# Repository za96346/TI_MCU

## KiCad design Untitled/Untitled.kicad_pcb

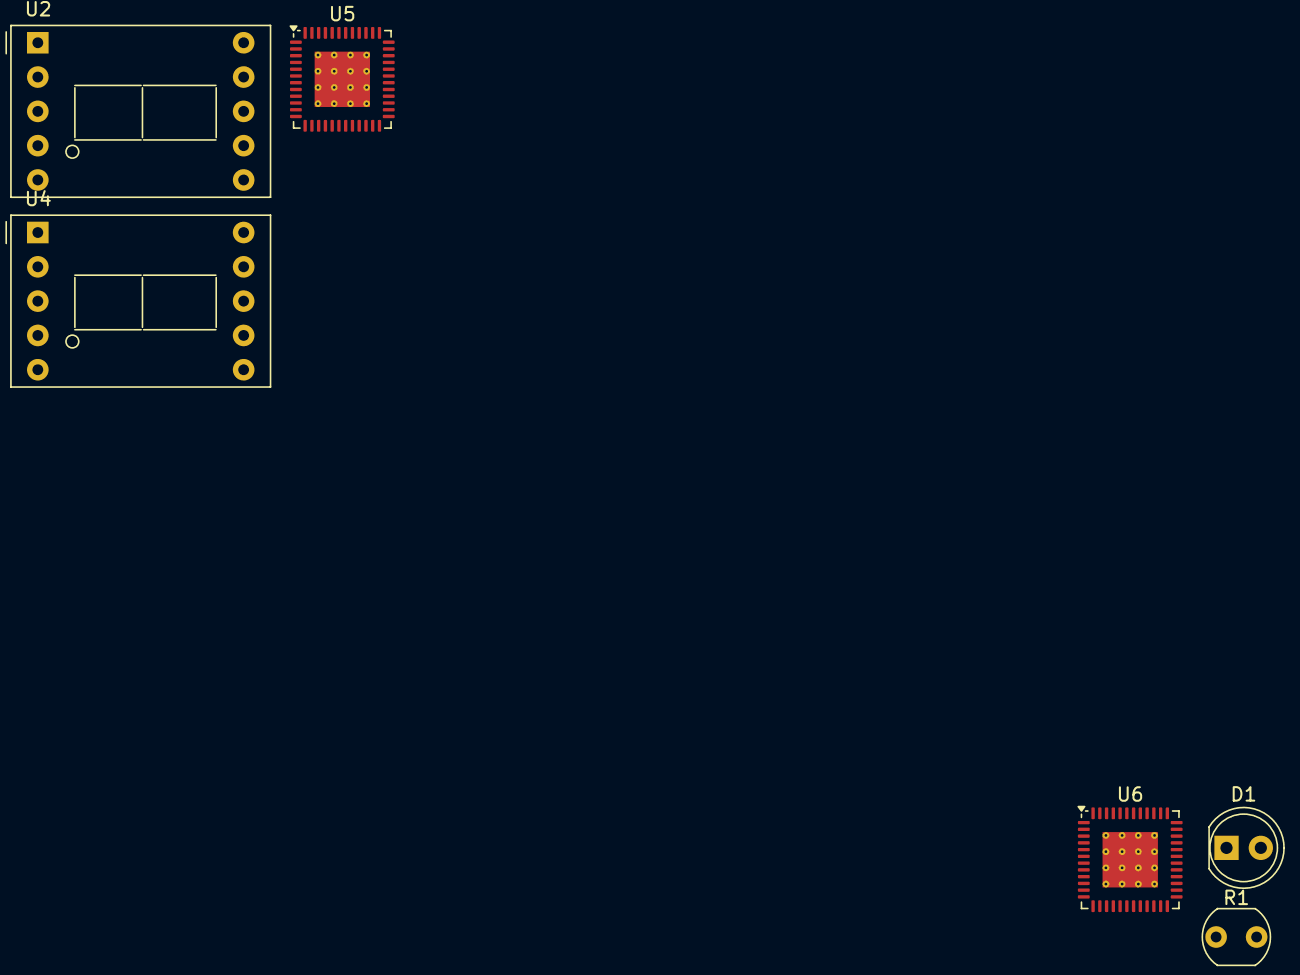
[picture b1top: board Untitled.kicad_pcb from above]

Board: 2 copper layers, 6 parts (0 on the bottom side), 10 nets, no tracks yet.

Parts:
D1: LD274; LED_D5.0mm_IRGrey
R1: A9013; R_LDR_5.0x4.1mm_P3mm_Vertical
U2, U4: D168K; D1X8K
U5, U6: CC430F5135xRGZ; VQFN-48-1EP_7x7mm_P0.5mm_EP4.1x4.1mm_ThermalVias

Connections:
GND: U2.3 (CC), U2.8 (CC), U4.3 (CC), U4.8 (CC)
unnamed: D1.1 (K), U6.8 (DVCC), U6.22 (DVCC), U6.41 (DVCC)
unnamed: D1.2 (A), U6.3 (P2.0)
unnamed: U5.27 (AVCC_RF), U5.28 (AVCC_RF)
unnamed: U5.31 (AVCC_RF), U5.32 (AVCC_RF)
unnamed: U5.8 (DVCC), U5.22 (DVCC), U5.41 (DVCC)
unnamed: U6.27 (AVCC_RF), U6.28 (AVCC_RF)
unnamed: U6.31 (AVCC_RF), U6.32 (AVCC_RF)
unnamed: R1.2, U6.12 (P1.1)
unnamed: R1.1, U6.49 (VSS)

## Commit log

2024-04-08 init
2024-04-08 chore: 移除 mode 判斷以及 Ｐ４init
2024-04-08 fix: 移除註解以及移除P2.3 interrept
2024-04-08 fix: 移除p4.1 中斷點
2024-04-08 fix: 移除PWM 相關code
2024-04-09 remove led duty cycle
2024-04-10 chore: 移除main.c 看不懂的
2024-04-10 chore: 移除無用引入, 並調整p5.2 邏輯
2024-04-10 chore: 調整
2024-04-10 chore: 加入 註解, u1/4
2024-11-27 chore
